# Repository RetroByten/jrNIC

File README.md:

# jrNIC
A simple project to build an initial prototype Network Interface Card and associated DOS driver code for the PCjr.

# Schematic:

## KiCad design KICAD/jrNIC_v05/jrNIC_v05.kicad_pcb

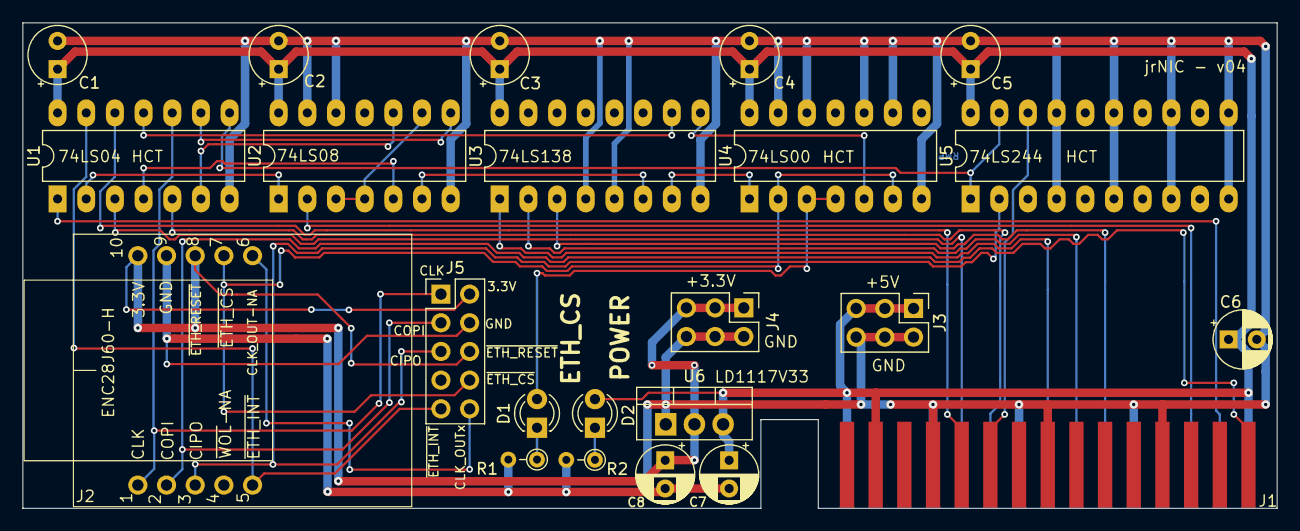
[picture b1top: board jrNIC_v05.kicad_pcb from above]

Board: 2 copper layers, 111.1 x 43.0 mm, 23 parts (0 on the bottom side), 31 nets.

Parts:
C1, C2, C3, C4, C5: 47pF; CP_Radial_Tantal_D5.0mm_P2.50mm
C6, C8: 10uF; CP_Radial_D5.0mm_P2.50mm
C7: 100nF; CP_Radial_D5.0mm_P2.50mm
D1, D2: LED; LED_D3.0mm
J1: PCjrModemPort
J2: Olimex_ENC28J60-H
J3, J4: Conn_02x03_Odd_Even; PinHeader_2x03_P2.54mm_Vertical
J5: Conn_02x05_Odd_Even; PinHeader_2x05_P2.54mm_Vertical
R1, R2: 120; R_Axial_DIN0204_L3.6mm_D1.6mm_P2.54mm_Vertical
U1: 74LS04; DIP-14_W7.62mm_LongPads
U2: 74LS08; DIP-14_W7.62mm_LongPads
U3: 74LS138; DIP-16_W7.62mm_LongPads
U4: 74LS00; DIP-14_W7.62mm_LongPads
U5: 74LS244; DIP-20_W7.62mm_LongPads
U6: TO-220-3_Vertical

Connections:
+3.3V: C8.1, J2.8 (~ETH_RESET), J2.10 (3.3V), J4.1, J4.3, J4.5, J5.2, J5.6, U6.2 (VOUT)
+5V: C1.1, C2.1, C3.1, C4.1, C5.1, C6.1, C7.1, D2.2 (A), J1.A14 (5V), J1.B1 (5V), J1.B15 (5V), J3.1, J3.3, J3.5, U1.14 (VCC), U2.14 (VCC), U3.16 (VCC), U4.14 (VCC), U5.20 (VCC), U6.3 (VIN)
/A0: J1.B8 (A0), U3.1 (A0)
/A1: J1.B7 (A1), U3.2 (A1)
/A2: J1.B6 (A2), U3.3 (A2)
/A9: J1.B3 (A9), U2.2
/CIPO: J2.3 (CIPO), J5.5, U5.2 (I0a)
/CLK: J2.1 (CLK), J5.1, U1.10
/CLK_OUTx: J2.6 (CLK_OUT), J5.10
/D0: J1.A10 (D0), U5.18 (O0a)
/D7: J1.A1 (D7), J2.2 (COPI), J5.3
/ETH_CS: D1.2 (A), U4.3, U4.4
/IOR: U1.6, U2.10
/IOW: U1.4, U2.5
/MODEM_CS: U1.2, U2.1
/MODEM_INT: J1.A11 (MODEM_INT), U1.12
/MODEM_PORT: U2.3, U2.4, U2.9
/READ_SELECT: U1.9, U2.8
/WRITE_SELECT: U2.6, U3.6 (E3)
/~CLK: U1.11, U3.10 (O5)
/~ETH_CS: J2.7 (~CS), J5.8, U4.2, U4.6
/~ETH_INT: J2.5 (~INT), J5.9, U1.13
/~IOR: J1.B10 (~IOR), U1.5
/~IOW: J1.B11 (~IOW), U1.3
/~LATCH_R: U3.9 (O6), U4.5
/~LATCH_S: U3.7 (O7), U4.1
/~MODEM_CS: J1.B2 (~MODEM_CS), U1.1
/~READ_SELECT: U1.8, U5.1 (OEa), U5.19 (OEb)
GND: C1.2, C2.2, C3.2, C4.2, C5.2, C6.2, C7.2, C8.2, J1.A4 (GND), J1.A8 (GND), J1.A12 (GND), J1.B5 (GND), J1.B9 (GND), J1.B12 (GND), J2.9 (GND), J3.2, J3.4, J3.6, J4.2, J4.4, J4.6, J5.4, R1.2, R2.2, U1.7 (GND), U2.7 (GND), U2.12, U2.13, U3.4 (E1), U3.5 (E2), U3.8 (GND), U4.7 (GND), U4.9, U4.10, U4.12, U4.13, U5.4 (I1a), U5.6 (I2a), U5.8 (I3a), U5.10 (GND), U5.11 (I0b), U5.13 (I1b), U5.15 (I2b), U5.17 (I3b), U6.1 (GND)
unnamed: D1.1 (K), R1.1
unnamed: D2.1 (K), R2.1

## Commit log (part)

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2024-07-08 Initial Commit of TSTPKTD program
2024-07-08 Fix 1, fixing the pkt_signature to be inside the interrupt handler itself
2024-07-09 Step 2: implementing some additional print utility functions
2024-07-10 Added a prototype cartridge version of the driver. Note that it currently requires external programs to convert the .COM file to the .BIN (adding the PCjr IPL header) and calculating the CRC (convert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
2024-07-12 Added TESTPKT4
2024-07-27 Implemented initial pass at SVC02 (access_type), fixed some bugs
2024-07-27 Implemented initial SVC03 support
2024-07-27 Implementing initial service 1
2024-07-27 Added initial support for service 6
2024-07-28 Initial hardware communication backend, implemented service 07 (reset) and service 04 (send)
2024-08-04 Initial RX commit, can successfully DHCP (sometimes) and FTP
2024-08-09 Skipping 11 (failed attempt), TSTPKT12 attempts to fix conflicting operations and a few other bugs
2024-08-25 Continuing to work on packet driver
2024-08-25 Added preliminary dimensions of original modem card in FreeCAD
2024-09-28 Added first attempt at PCB
2024-10-27 Updated jrNIC KICAD to v04, which fixes the ethernet devboard pin sizing issue and adds some headers to make debugging easier
2024-10-27 Removing DOS stuff from the PCB dev branch for clarity
2024-10-27 Removing KICAD/FREECAD from packet driver branch for clarity
2024-10-27 Changed Ethernet DevBoard footprint
2024-12-16 Working on adding function/macro headers and rebuilding the driver to be cartridge loadable
2024-12-17 Added comments and test cases for read/write buffer memory byte/word
2024-12-18 Added read/write buffer memory function, aprint memory function, and clear card memory function
2024-12-20 Added read/write PHY register functions
2024-12-23 Finished TEST functions, started working on HAL_INIT
2024-12-24 Continuing INIT_HAL function development
2024-12-29 Working on HW interrupt / receive function
2025-01-16 Making progress on receive, supporting multiple handles, and receive having an internal stack / suppressing NMI
2025-01-16 Working on re-implementing the services
2025-01-19 Making progress, works with sending and receiving but not both
2025-03-08 Modified receive function entry, seems to better match the behavior of the previous driver now
2025-10-09 COM only driver, 2nd full pass
2025-10-09 Only enabling RX when access_type() is called
2025-10-16 Merging in stable enough v1
2025-10-20 Moved IRQ_RECV into SHIM
2025-10-20 Added entry shim for INT_PKT, noted current issue with an intermittent fault that seems to be tied to NMI firing (typing) on DOS prompt while netdrive is connected and the network is sending/recevivi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
2025-10-20 added MAIN enable ints
2025-10-20 Seemed to work for now. Technially the IRQ stack swap is now not protected which should be revisited at some point
2025-10-20 Added comment
2025-10-25 Added initial cartridge header, moved mac address and variable definitions in memory shim, added program signature segment pointer
2025-10-25 (actual commit)Added initial cartridge header, moved mac address and variable definitions in memory shim, added program signature segment pointer
2025-10-28 First full pass at supporting ROM driver stored on a cartridge
2025-11-19 Working on v5
